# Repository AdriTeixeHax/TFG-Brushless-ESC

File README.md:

# RTSpeed
 FOC destined controller

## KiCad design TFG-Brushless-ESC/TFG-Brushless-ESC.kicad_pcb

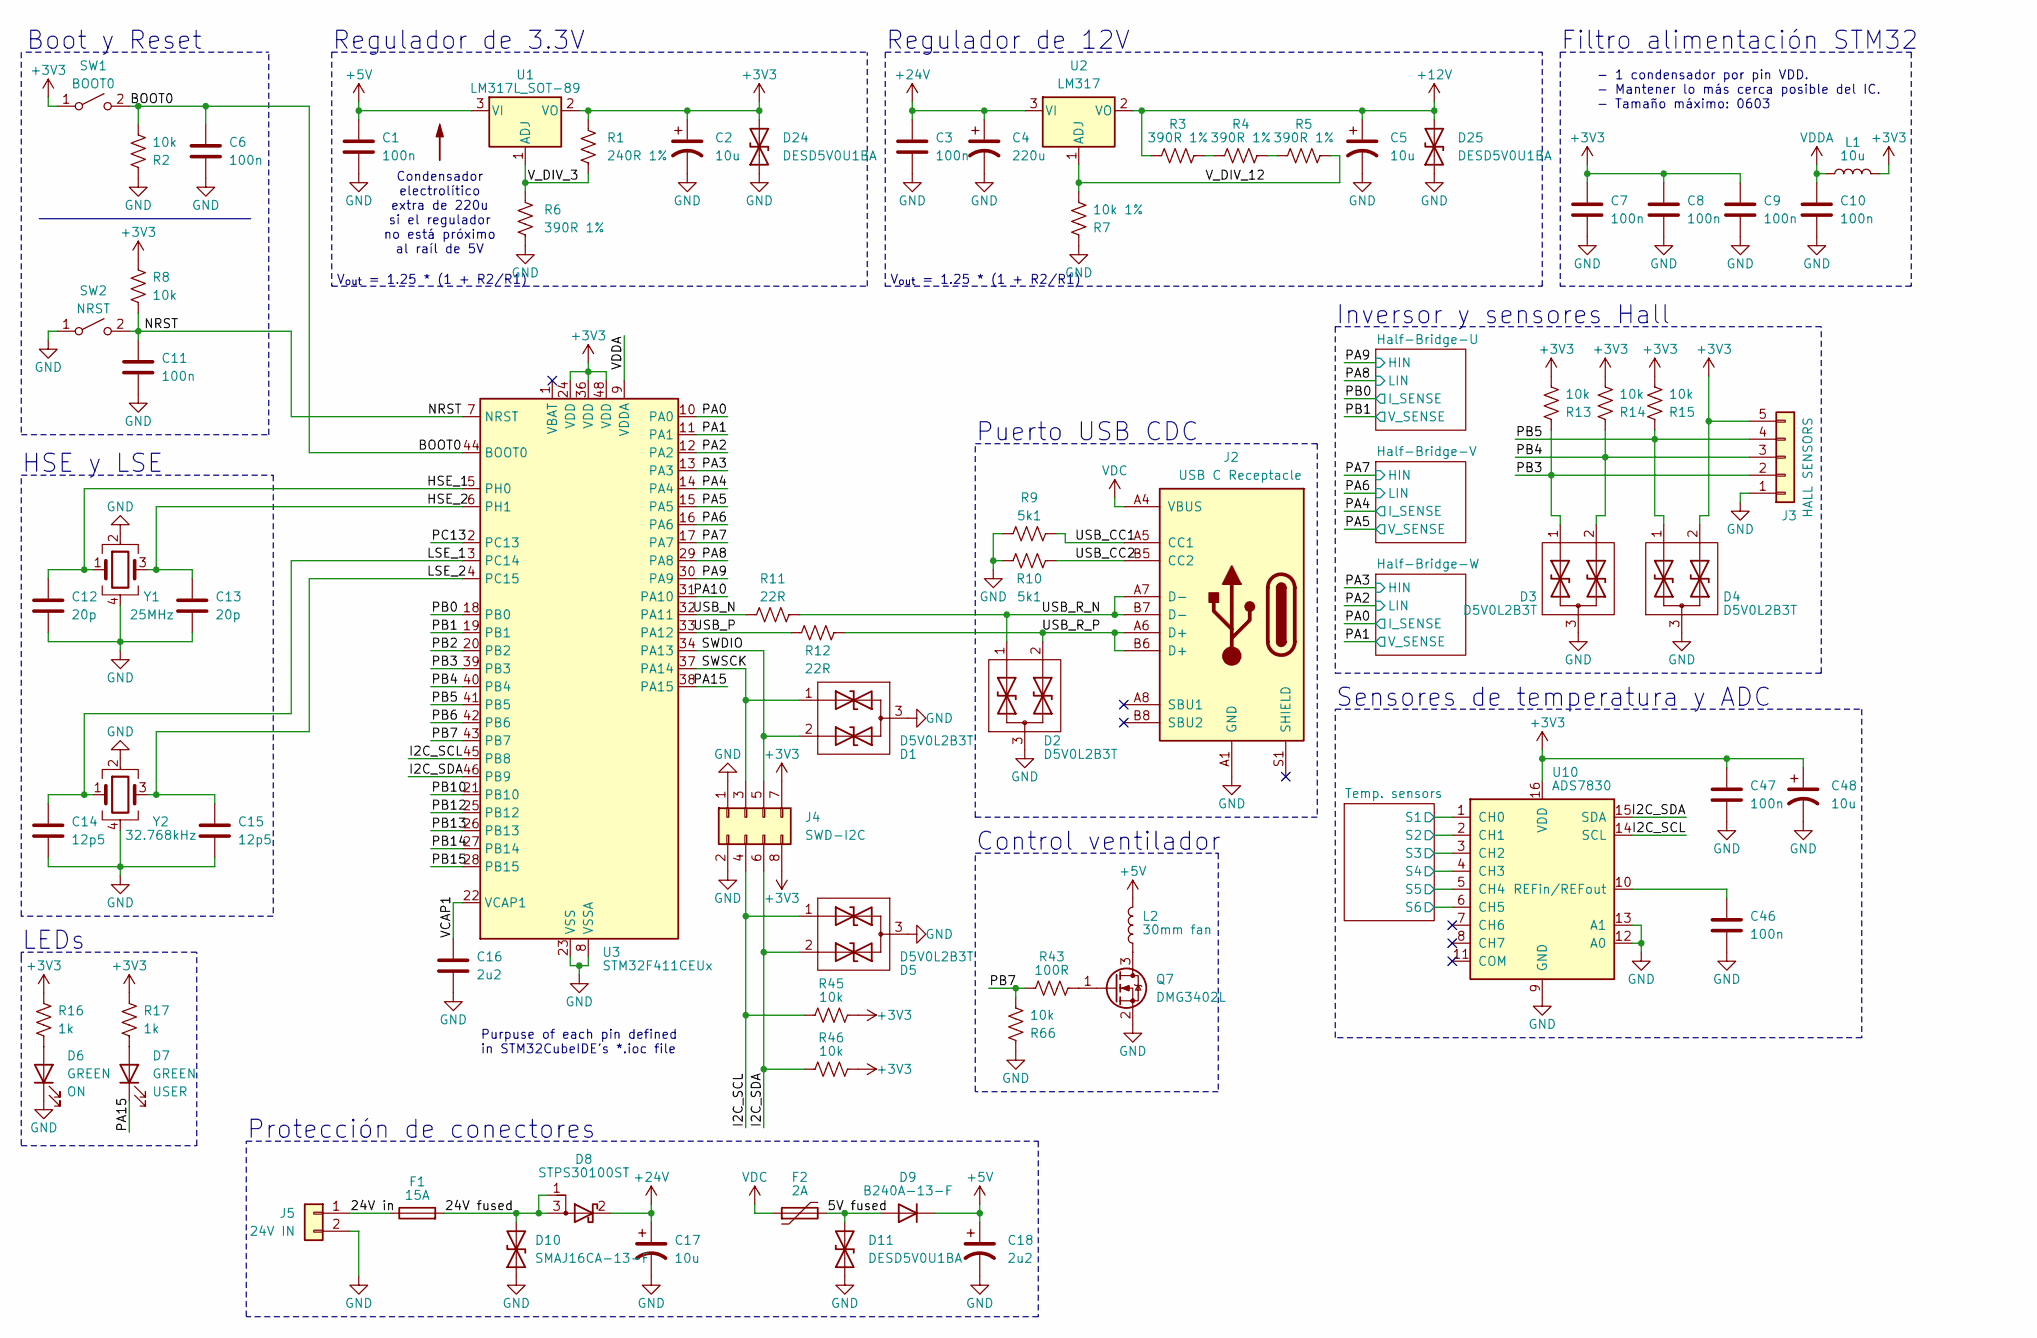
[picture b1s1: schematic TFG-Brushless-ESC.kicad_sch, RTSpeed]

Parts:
C1, C3, C6, C7, C8, C9, C10, C11, C46, C47: 100n; C_0603_1608Metric
C2, C5, C17, C48: 10u; CP_Elec_4x5.4
C4: 220u; CP_Elec_4x5.4
C12, C13: 20p; C_0603_1608Metric
C14, C15: 12p5; C_0603_1608Metric
C16: 2u2; C_0603_1608Metric
C18: 2u2; CP_Elec_4x5.4
D1, D2, D3, D4, D5: D5V0L2B3T; SOT-523
D6, D7: GREEN; LED_0805_2012Metric
D8: STPS30100ST; TO-220-3_Vertical
D9: B240A-13-F; D_SMA
D10: SMAJ16CA-13-F; D_SMA
D11, D24, D25: DESD5V0U1BA; D_SOD-323_HandSoldering
F1: 15A; Fuseholder_Automotive
F2: 2A; Fuse_1812_4532Metric
J2: USB C Receptacle; USB_C_Receptacle_XKB_U262-16XN-4BVC11
J3: HALL SENSORS; JST_PH_S5B-PH-K_1x05_P2.00mm_Horizontal
J4: SWD-I2C; PinHeader_2x04_P2.54mm_Horizontal
J5: 24V IN; PhoenixContact_MSTBA_2,5_2-G-5,08_1x02_P5.08mm_Horizontal
L1: 10u; L_0805_2012Metric
L2: 30mm fan; PinHeader_1x02_P2.54mm_Vertical
Q7: DMG3402L; SOT-23
R1: 240R 1%; R_0603_1608Metric
R2, R8, R13, R14, R15, R45, R46, R66: 10k; R_0603_1608Metric
R3, R4, R5, R6: 390R 1%; R_0603_1608Metric
R7: 10k 1%; R_0603_1608Metric
R9, R10: 5k1; R_0603_1608Metric
R11, R12: 22R; R_0603_1608Metric
R16, R17: 1k; R_0603_1608Metric
R43: 100R; R_0805_2012Metric
SW1: BOOT0; SW_Push_1P1T_NO_6x6mm_H9.5mm
SW2: NRST; SW_Push_1P1T_NO_6x6mm_H9.5mm
U1: LM317L_SOT-89; SOT-89-3
U2: LM317; TO-220-3_Vertical
U3: STM32F411CEUx; QFN-48-1EP_7x7mm_P0.5mm_EP5.6x5.6mm
U10: ADS7830; TSSOP-16_4.4x5mm_P0.65mm
Y1: 25MHz; Oscillator_SMD_Abracon_ASE-4Pin_3.2x2.5mm
Y2: 32.768kHz; Oscillator_SMD_Abracon_ASE-4Pin_3.2x2.5mm

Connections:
+3V3: C2.1, C7.1, C8.1, C9.1, C47.1, C48.1, D4.2, D24.2 (A2), J3.5, J4.7, J4.8, L1.2, R1.1, R8.1, R13.2, R14.2, R15.2, R16.1, R17.1, R45.2, R46.2, SW1.1 (A), U1.2 (VO), U3.24 (VDD), U3.36 (VDD), U3.48 (VDD), U10.16 (VDD); also elsewhere on the board
+5V: C1.1, C18.1, D9.1 (K), L2.2, U1.3 (VI)
+12V: C5.1, D25.2 (A2), R3.1, U2.2 (VO); also elsewhere on the board
+24V: C3.1, C4.1, C17.1, D8.2 (K), U2.3 (VI); also elsewhere on the board
/5V fused: D9.2 (A), D11.2 (A2), F2.2
/24V fused: D8.1 (A), D8.3 (A), D10.2 (A2), F1.2
/24V in: F1.1, J5.1
/BOOT0: C6.2, R2.2, SW1.2 (B), U3.44 (BOOT0)
/HSE_1: C12.1, U3.5 (PH0), Y1.1
/HSE_2: C13.1, U3.6 (PH1), Y1.3
/I2C_SCL: D5.1, J4.4, R45.1, U3.45 (PB8), U10.14 (SCL)
/I2C_SDA: D5.2, J4.6, R46.1, U3.46 (PB9), U10.15 (SDA)
/LSE_1: C14.1, U3.3 (PC14), Y2.1
/LSE_2: C15.1, U3.4 (PC15), Y2.3
/NRST: C11.2, R8.2, SW2.2 (B), U3.7 (NRST)
/PA0: U3.10 (PA0); also elsewhere on the board
/PA1: U3.11 (PA1); also elsewhere on the board
/PA2: U3.12 (PA2); also elsewhere on the board
/PA3: U3.13 (PA3); also elsewhere on the board
/PA4: U3.14 (PA4); also elsewhere on the board
/PA5: U3.15 (PA5); also elsewhere on the board
/PA6: U3.16 (PA6); also elsewhere on the board
/PA7: U3.17 (PA7); also elsewhere on the board
/PA8: U3.29 (PA8); also elsewhere on the board
/PA9: U3.30 (PA9); also elsewhere on the board
/PA10: U3.31 (PA10)
/PA15: D7.1 (K), U3.38 (PA15)
/PB0: U3.18 (PB0); also elsewhere on the board
/PB1: U3.19 (PB1); also elsewhere on the board
/PB2: U3.20 (PB2)
/PB3: D3.1, J3.2, R13.1, U3.39 (PB3)
/PB4: D3.2, J3.3, R14.1, U3.40 (PB4)
/PB5: D4.1, J3.4, R15.1, U3.41 (PB5)
/PB6: U3.42 (PB6)
/PB7: R43.1, R66.2, U3.43 (PB7)
/PB10: U3.21 (PB10)
/PB12: U3.25 (PB12)
/PB13: U3.26 (PB13)
/PB14: U3.27 (PB14)
/PB15: U3.28 (PB15)
/PC13: U3.2 (PC13)
/SWDIO: D1.2, J4.5, U3.34 (PA13)
/SWSCK: D1.1, J4.3, U3.37 (PA14)
/Temp. sensors/S1: U10.1 (CH0); also elsewhere on the board
/Temp. sensors/S2: U10.2 (CH1); also elsewhere on the board
/Temp. sensors/S3: U10.3 (CH2); also elsewhere on the board
/Temp. sensors/S4: U10.4 (CH3); also elsewhere on the board
/Temp. sensors/S5: U10.5 (CH4); also elsewhere on the board
/Temp. sensors/S6: U10.6 (CH5); also elsewhere on the board
/USB_CC1: J2.A5 (CC1), R9.2
/USB_CC2: J2.B5 (CC2), R10.2
/USB_N: R11.1, U3.32 (PA11)
/USB_P: R12.1, U3.33 (PA12)
/USB_R_N: D2.1, J2.A7 (D-), J2.B7 (D-), R11.2
/USB_R_P: D2.2, J2.A6 (D+), J2.B6 (D+), R12.2
/VCAP1: C16.1, U3.22 (VCAP1)
/V_DIV_3: R1.2, R6.1, U1.1 (ADJ)
/V_DIV_12: R5.2, R7.2, U2.1 (ADJ)
GND: C1.2, C2.2, C3.2, C4.2, C5.2, C6.1, C7.2, C8.2, C9.2, C10.2, C11.1, C12.2, C13.2, C14.2, C15.2, C16.2, C17.2, C18.2, C46.2, C47.2, C48.2, D1.3, D2.3, D3.3, D4.3, D5.3, D6.1 (K), D10.1 (A1), D11.1 (A1), D24.1 (A1), D25.1 (A1), J2.A1 (GND), J2.A12 (GND), J2.B1 (GND), J2.B12 (GND), J3.1, J4.1, J4.2, J5.2, Q7.2 (S), R2.1, R6.2, R7.1, R9.1, R10.1, R66.1, SW2.1 (A), U3.8 (VSSA), U3.23 (VSS), U3.35 (VSS), U3.47 (VSS), U3.49 (VSS), U10.9 (GND), U10.12 (A0), U10.13 (A1), Y1.2, Y1.4, Y2.2, Y2.4; also elsewhere on the board
unnamed: D6.2 (A), R16.2
unnamed: D7.2 (A), R17.2
unnamed: L2.1, Q7.3 (D)
unnamed: Q7.1 (G), R43.2
unnamed: R3.2, R4.1
unnamed: R4.2, R5.1
unnamed: C46.1, U10.10 (REFin/REFout)
VDC: F2.1, J2.A4 (VBUS), J2.A9 (VBUS), J2.B4 (VBUS), J2.B9 (VBUS)
VDDA: C10.1, L1.1, U3.9 (VDDA)

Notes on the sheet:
Control ventilador
V_{out} = 1.25 * (1 + R2/R1)
Boot y Reset
LEDs
Regulador de 3.3V
Filtro alimentación STM32
Protección de conectores
- 1 condensador por pin VDD. - Mantener lo más cerca posible del IC. - Tamaño máximo: 0603
Inversor y sensores Hall
Puerto USB CDC
Sensores de temperatura y ADC
Regulador de 12V
HSE y LSE
Purpuse of each pin defined in STM32CubeIDE's *.ioc file
Condensador electrolítico extra de 220u si el regulador no está próximo al raíl de 5V

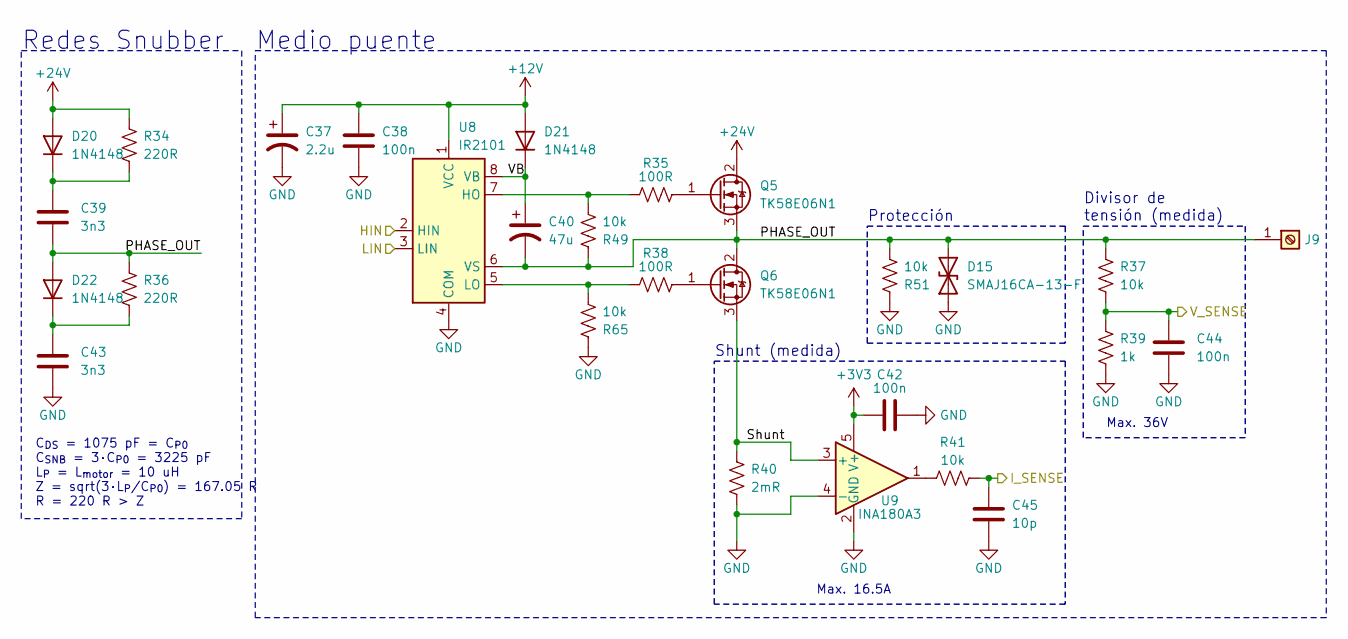
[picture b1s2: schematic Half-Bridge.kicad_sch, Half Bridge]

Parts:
C37: 2.2u; CP_Elec_4x5.4
C38, C42, C44: 100n; C_0603_1608Metric
C39, C43: 3n3; C_0603_1608Metric
C40: 47u; CP_Elec_4x5.4
C45: 10p; C_0603_1608Metric
D15: SMAJ16CA-13-F; D_SMA
D20, D21, D22: 1N4148; D_SOD-123
J9: Screw_Terminal; LCSC part C481447
Q5, Q6: TK58E06N1; TO-220-3_Vertical
R34, R36: 220R; R_0603_1608Metric
R35, R38: 100R; R_0805_2012Metric
R37, R41, R49, R51, R65: 10k; R_0603_1608Metric
R39: 1k; R_0603_1608Metric
R40: 2mR; R_2512_6332Metric
U8: IR2101; SOIC-8-1EP_3.9x4.9mm_P1.27mm_EP2.29x3mm
U9: INA180A3; SOT-23-5

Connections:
+3V3: C42.1, U9.5 (V+); also elsewhere on the board
+12V: C37.1, C38.1, D21.2 (A), U8.1 (VCC); also elsewhere on the board
+24V: D20.2 (A), Q5.2 (D), R34.2; also elsewhere on the board
/Half-Bridge-W/Shunt: Q6.3 (S), R40.1, U9.3 (+)
/Half-Bridge-W/VB: C40.1, D21.1 (K), U8.8 (VB)
/PA0: C45.2, R41.2; also elsewhere on the board
/PA1: C44.1, R37.1, R39.2; also elsewhere on the board
/PA2: U8.3 (LIN); also elsewhere on the board
/PA3: U8.2 (HIN); also elsewhere on the board
GND: C37.2, C38.2, C42.2, C43.2, C44.2, C45.1, D15.1 (A1), R39.1, R40.2, R51.1, R65.1, U8.4 (COM), U9.2 (GND), U9.4 (-); also elsewhere on the board
unnamed: C39.1, D20.1 (K), R34.1
unnamed: C43.1, D22.1 (K), R36.1
unnamed: Q5.1 (G), R35.2
unnamed: Q6.1 (G), R38.2
unnamed: R41.1, U9.1
unnamed: R35.1, R49.2, U8.7 (HO)
unnamed: R38.1, R65.2, U8.5 (LO)

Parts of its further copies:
C19, C28: 2.2u; CP_Elec_4x5.4
C20, C24, C26, C29, C33, C35: 100n; C_0603_1608Metric
C21, C25, C30, C34: 3n3; C_0603_1608Metric
C22, C31: 47u; CP_Elec_4x5.4
C27, C36: 10p; C_0603_1608Metric
D12, D13, D14, D16, D17, D18: 1N4148; D_SOD-123
D19, D23: SMAJ16CA-13-F; D_SMA
J6, J8: Screw_Terminal; LCSC part C481447
Q1, Q2, Q3, Q4: TK58E06N1; TO-220-3_Vertical
R18, R20, R26, R28: 220R; R_0603_1608Metric
R19, R22, R27, R30: 100R; R_0805_2012Metric
R21, R25, R29, R33, R42, R47, R48, R50, R63, R64: 10k; R_0603_1608Metric
R23, R31: 1k; R_0603_1608Metric
R24, R32: 2mR; R_2512_6332Metric
U4, U6: IR2101; SOIC-8-1EP_3.9x4.9mm_P1.27mm_EP2.29x3mm
U5, U7: INA180A3; SOT-23-5

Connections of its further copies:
+3V3: C24.1, C33.1, U5.5 (V+), U7.5 (V+); also elsewhere on the board
+12V: C19.1, C20.1, C28.1, C29.1, D13.2 (A), D17.2 (A), U4.1 (VCC), U6.1 (VCC); also elsewhere on the board
+24V: D12.2 (A), D16.2 (A), Q1.2 (D), Q3.2 (D), R18.2, R26.2; also elsewhere on the board
/Half-Bridge-U/Shunt: Q2.3 (S), R24.1, U5.3 (+)
/Half-Bridge-U/VB: C22.1, D13.1 (K), U4.8 (VB)
/Half-Bridge-V/PHASE_OUT: C30.2, C31.2, D18.2 (A), D19.2 (A2), J8.1, Q3.3 (S), Q4.2 (D), R28.2, R29.2, R48.1, R50.2, U6.6 (VS)
/Half-Bridge-V/Shunt: Q4.3 (S), R32.1, U7.3 (+)
/Half-Bridge-V/VB: C31.1, D17.1 (K), U6.8 (VB)
/PA4: C36.2, R33.2; also elsewhere on the board
/PA5: C35.1, R29.1, R31.2; also elsewhere on the board
/PA6: U6.3 (LIN); also elsewhere on the board
/PA7: U6.2 (HIN); also elsewhere on the board
/PA8: U4.3 (LIN); also elsewhere on the board
/PA9: U4.2 (HIN); also elsewhere on the board
/PB0: C27.2, R25.2; also elsewhere on the board
/PB1: C26.1, R21.1, R23.2; also elsewhere on the board
GND: C19.2, C20.2, C24.2, C25.2, C26.2, C27.1, C28.2, C29.2, C33.2, C34.2, C35.2, C36.1, D19.1 (A1), D23.1 (A1), R23.1, R24.2, R31.1, R32.2, R42.1, R50.1, R63.1, R64.1, U4.4 (COM), U5.2 (GND), U5.4 (-), U6.4 (COM), U7.2 (GND), U7.4 (-); also elsewhere on the board
unnamed: C21.1, D12.1 (K), R18.1
unnamed: C25.1, D14.1 (K), R20.1
unnamed: C30.1, D16.1 (K), R26.1
unnamed: C34.1, D18.1 (K), R28.1
unnamed: Q1.1 (G), R19.2
unnamed: Q2.1 (G), R22.2
unnamed: Q3.1 (G), R27.2
unnamed: Q4.1 (G), R30.2
unnamed: R25.1, U5.1
unnamed: R33.1, U7.1
unnamed: R19.1, R47.2, U4.7 (HO)
unnamed: R22.1, R63.2, U4.5 (LO)
unnamed: R27.1, R48.2, U6.7 (HO)
unnamed: R30.1, R64.2, U6.5 (LO)

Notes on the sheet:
Max. 36V
Protección
Divisor de tensión (medida)
Medio puente
C_{DS} = 1075 pF = C_{P0} C_{SNB} = 3·C_{P0} = 3225 pF L_{P} = L_{motor} = 10 uH Z = sqrt(3·L_{P}/C_{P0}) = 167.05 R R = 220 R > Z
Max. 16.5A
Redes Snubber
Shunt (medida)

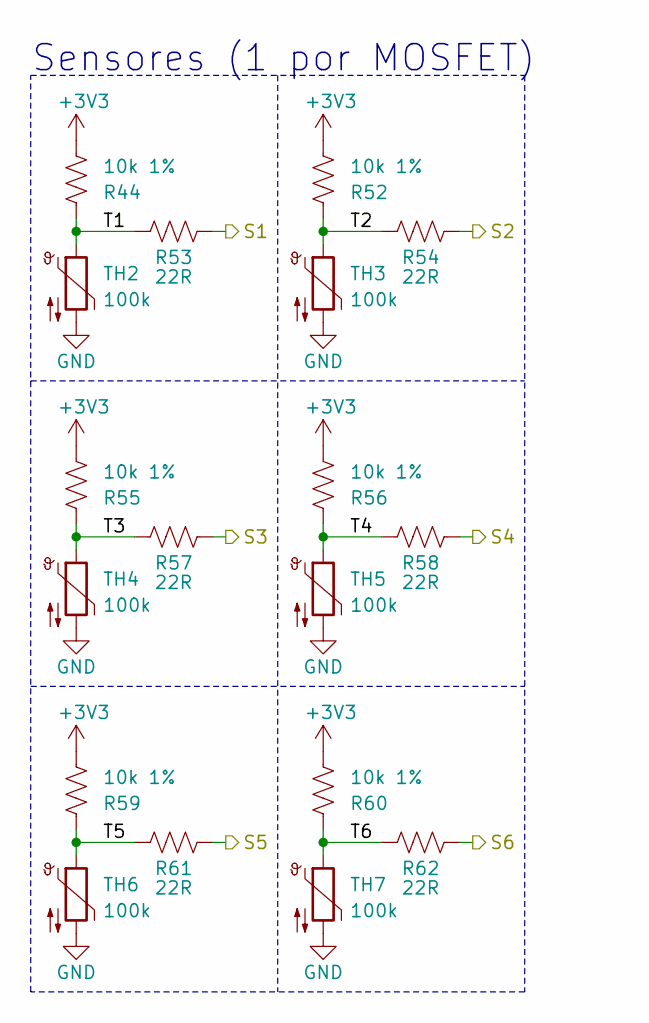
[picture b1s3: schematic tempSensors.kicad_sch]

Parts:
R44, R52, R55, R56, R59, R60: 10k 1%; R_0603_1608Metric
R53, R54, R57, R58, R61, R62: 22R; R_0603_1608Metric
TH2, TH3, TH4, TH5, TH6, TH7: 100k; PinHeader_1x02_P2.54mm_Vertical

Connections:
+3V3: R44.2, R52.2, R55.2, R56.2, R59.2, R60.2; also elsewhere on the board
/Temp. sensors/S1: R53.1; also elsewhere on the board
/Temp. sensors/S2: R54.1; also elsewhere on the board
/Temp. sensors/S3: R57.1; also elsewhere on the board
/Temp. sensors/S4: R58.1; also elsewhere on the board
/Temp. sensors/S5: R61.1; also elsewhere on the board
/Temp. sensors/S6: R62.1; also elsewhere on the board
/Temp. sensors/T1: R44.1, R53.2, TH2.1
/Temp. sensors/T2: R52.1, R54.2, TH3.1
/Temp. sensors/T3: R55.1, R57.2, TH4.1
/Temp. sensors/T4: R56.1, R58.2, TH5.1
/Temp. sensors/T5: R59.1, R61.2, TH6.1
/Temp. sensors/T6: R60.1, R62.2, TH7.1
GND: TH2.2, TH3.2, TH4.2, TH5.2, TH6.2, TH7.2; also elsewhere on the board

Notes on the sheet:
Sensores (1 por MOSFET)

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
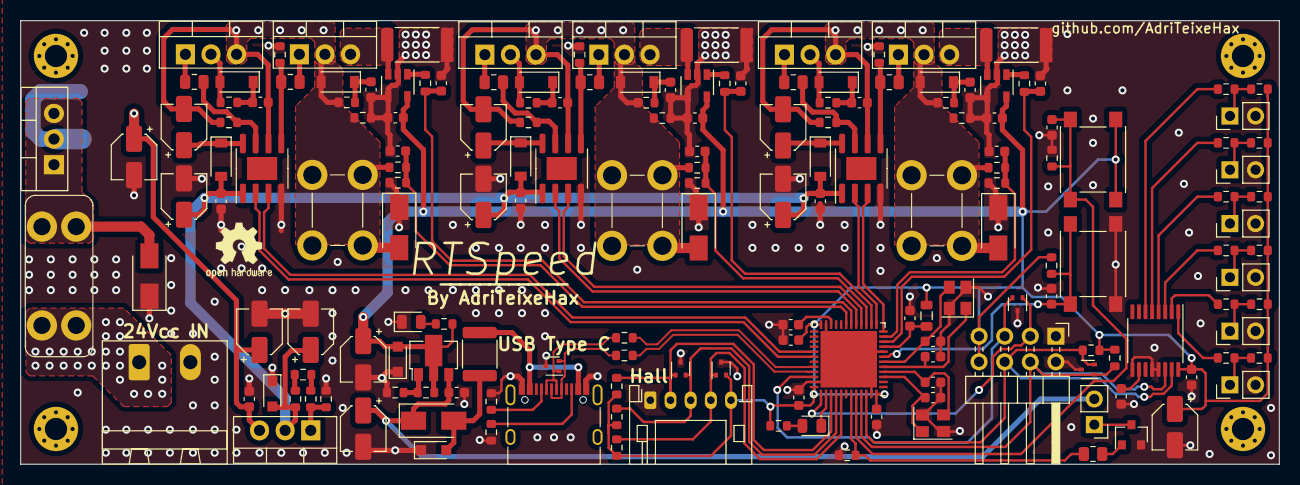
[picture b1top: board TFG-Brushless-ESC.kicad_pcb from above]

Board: 4 copper layers, 124.9 x 44.0 mm, 174 parts (0 on the bottom side), 95 nets.

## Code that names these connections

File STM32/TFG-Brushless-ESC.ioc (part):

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Mcu.Name=STM32F411C(C-E)Ux
Mcu.Package=UFQFPN48
Mcu.UserName=STM32F411CEUx
PA0-WKUP.GPIOParameters=GPIO_Label
PA0-WKUP.GPIO_Label=I_SENSE_W
PA0-WKUP.Signal=ADCx_IN0
PA1.GPIOParameters=GPIO_Label
PA1.GPIO_Label=V_SENSE_W
PA1.Signal=ADCx_IN1
PA11.Mode=Device_Only
PA11.Signal=USB_OTG_FS_DM
PA12.Mode=Device_Only
PA12.Signal=USB_OTG_FS_DP
PA13.Mode=Serial_Wire
PA13.Signal=SYS_JTMS-SWDIO
PA14.Mode=Serial_Wire
PA14.Signal=SYS_JTCK-SWCLK
PA15.GPIOParameters=GPIO_Label
PA15.GPIO_Label=N_USER_LED
PA15.Signal=GPIO_Output
PA2.GPIOParameters=GPIO_Label
PA2.GPIO_Label=LO_W
PA2.Signal=S_TIM2_CH3
PA3.GPIOParameters=GPIO_Label
PA3.GPIO_Label=HI_W
PA3.Signal=S_TIM2_CH4
PA4.GPIOParameters=GPIO_Label
PA4.GPIO_Label=I_SENSE_V
PA4.Signal=ADCx_IN4
PA5.GPIOParameters=GPIO_Label
PA5.GPIO_Label=V_SENSE_V
PA5.Signal=ADCx_IN5
PA6.GPIOParameters=GPIO_Label
PA6.GPIO_Label=LO_V
PA6.Signal=S_TIM3_CH1
PA7.GPIOParameters=GPIO_Label
PA7.GPIO_Label=HI_V
PA7.Signal=S_TIM3_CH2
PA8.GPIOParameters=GPIO_Label
PA8.GPIO_Label=LO_U
PA8.Signal=S_TIM1_CH1
PA9.GPIOParameters=GPIO_Label
PA9.GPIO_Label=HI_U
PA9.Signal=S_TIM1_CH2
PB0.GPIOParameters=GPIO_Label
PB0.GPIO_Label=I_SENSE_U
PB0.Signal=ADCx_IN8
PB1.GPIOParameters=GPIO_Label
PB1.GPIO_Label=V_SENSE_U
PB1.Signal=ADCx_IN9
PB3.GPIOParameters=GPIO_Label
PB3.GPIO_Label=HALL_W
PB3.Signal=GPXTI3
PB4.GPIOParameters=GPIO_Label
PB4.GPIO_Label=HALL_V
PB4.Signal=GPXTI4
PB5.GPIOParameters=GPIO_Label
PB5.GPIO_Label=HALL_U
PB5.Signal=GPXTI5
PB7.GPIOParameters=GPIO_Label
PB7.GPIO_Label=FAN_CTRL
PB7.Signal=S_TIM4_CH2
PB8.Mode=I2C
PB8.Signal=I2C1_SCL
PB9.Mode=I2C
PB9.Signal=I2C1_SDA
PC14-OSC32_IN.Mode=LSE-External-Oscillator
PC14-OSC32_IN.Signal=RCC_OSC32_IN
PC15-OSC32_OUT.Mode=LSE-External-Oscillator
PC15-OSC32_OUT.Signal=RCC_OSC32_OUT
PH0\ -\ OSC_IN.Mode=HSE-External-Oscillator
PH0\ -\ OSC_IN.Signal=RCC_OSC_IN
PH1\ -\ OSC_OUT.Mode=HSE-External-Oscillator
PH1\ -\ OSC_OUT.Signal=RCC_OSC_OUT
RCC.HSE_VALUE=25000000
RCC.SYSCLKFreq_VALUE=25000000
RCC.SYSCLKSource=RCC_SYSCLKSOURCE_HSE
board=custom

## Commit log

2024-01-30 Working data sending example
2024-02-02 Initial code
2024-02-04 Updated arduino serial timeout
2024-02-04 Working transmit test (sinewave)
2024-02-09 Updated gitignore
2024-02-10 Half bridge design
2024-02-11 Added STM32F411 development schematic
2024-02-11 Connected Inverter
2024-02-12 Data can now be recieved through CDC to set sinewave frequency
2024-02-20 updated inverter model
2024-04-05 Added some footprints
2024-04-30 Renaming
2024-04-30 Renaming 2
2024-07-10 Changes in half-bridge
    Corrected voltage from 48 to 24V and 5V Vcc to 12V Vcc
2024-07-16 Attempt at implementing regenerative braking
2024-07-17 Figured out regenerative braking
2024-07-17 Added current and voltage sensing
    Other changes: removed BAT Diode since it will not be used, renamed pins of STM32
2024-07-18 Added simple code to test PWM
2024-08-03 STM and Eeschema changes
    STM tests and fixed MOSFET error in Half Bridge
2024-08-07 Footprint corrections
2024-08-07 Half bridges done
2024-08-08 Switched stackup and routed part of uC
2024-09-08 Changes in schematic and pcb
2024-09-19 temporary unifinished layout
    tht components and initia layout
2024-09-19 cleaned layout
2024-11-25 updated arduino code to send correct testing messages to windows app
2024-12-23 updated code to match pinout
2025-01-12 Added pulldown resistors at motor output
2025-01-18 Slight code changes
2025-02-02 Added images and stm code cleanup
2025-02-02 Change motor terminal blocks and new half bridge layaout
2025-02-06 PCB v2
2025-02-08 PCB v3
2025-02-08 Changed layout in ioc file. NOT IN CODE
2025-02-08 updated main power connector to phoenix
2025-02-09 renaming images
2025-02-10 Added fan control and temp measurement. Not added to pcb yet
2025-02-11 Added temperature sensors per phase and adc
2025-02-13 Added pulldown resistors for the half bridge mosfets, fan mosfet and fixed code pinout
2025-02-13 Traducción nombres
2025-02-13 mas traducciones
2025-02-13 more separation between traces
2025-02-13 minor pcb fixes and start of analog implementation
